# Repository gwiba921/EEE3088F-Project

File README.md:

# EEE3088F-Project
# EEE3088F Project: Power Subsystem for Micro Mouse Robot

## 📌 Introduction

This project forms part of the EEE3088F course, focusing on the design and development of the **power subsystem** for a maze-solving robot known as a **micro mouse**. The micro mouse achieves autonomous navigation through a system modularized into:

- Processor
- Motherboard
- Sensing
- Power

Our responsibility lies in the **Power Module**, which ensures reliable power delivery to all electronic components of the micro mouse.

---

## ⚙️ 1. Problem Description

The micro mouse requires a stable and efficient power supply to drive its operations, which include movement, sensing, and computation. This project involves designing a power module capable of:

- Powering **four DC motors**
- Integrating **USB-C** for **9V output**
- Regulating **3.3V and 5V power rails**
- Enabling **dual battery charging modes**

All of this must be done while maintaining modular compatibility with the rest of the micro mouse system.

---

## 📐 2. Scope and Limitations

- **Scope**:  
  This project is limited to the **power subsystem only**. However, the design must remain compatible with the processor, motherboard, and sensing modules.

- **Constraints**:
  - Strict budget limit of **$70**
  - **No use of breadboard-based components**
  - Must meet **PCB dimension limits**: `82mm x 60mm`
  - Requires **individual reports** despite collaborative PCB design
  - PCB must be designed from scratch using **permitted components only**

---

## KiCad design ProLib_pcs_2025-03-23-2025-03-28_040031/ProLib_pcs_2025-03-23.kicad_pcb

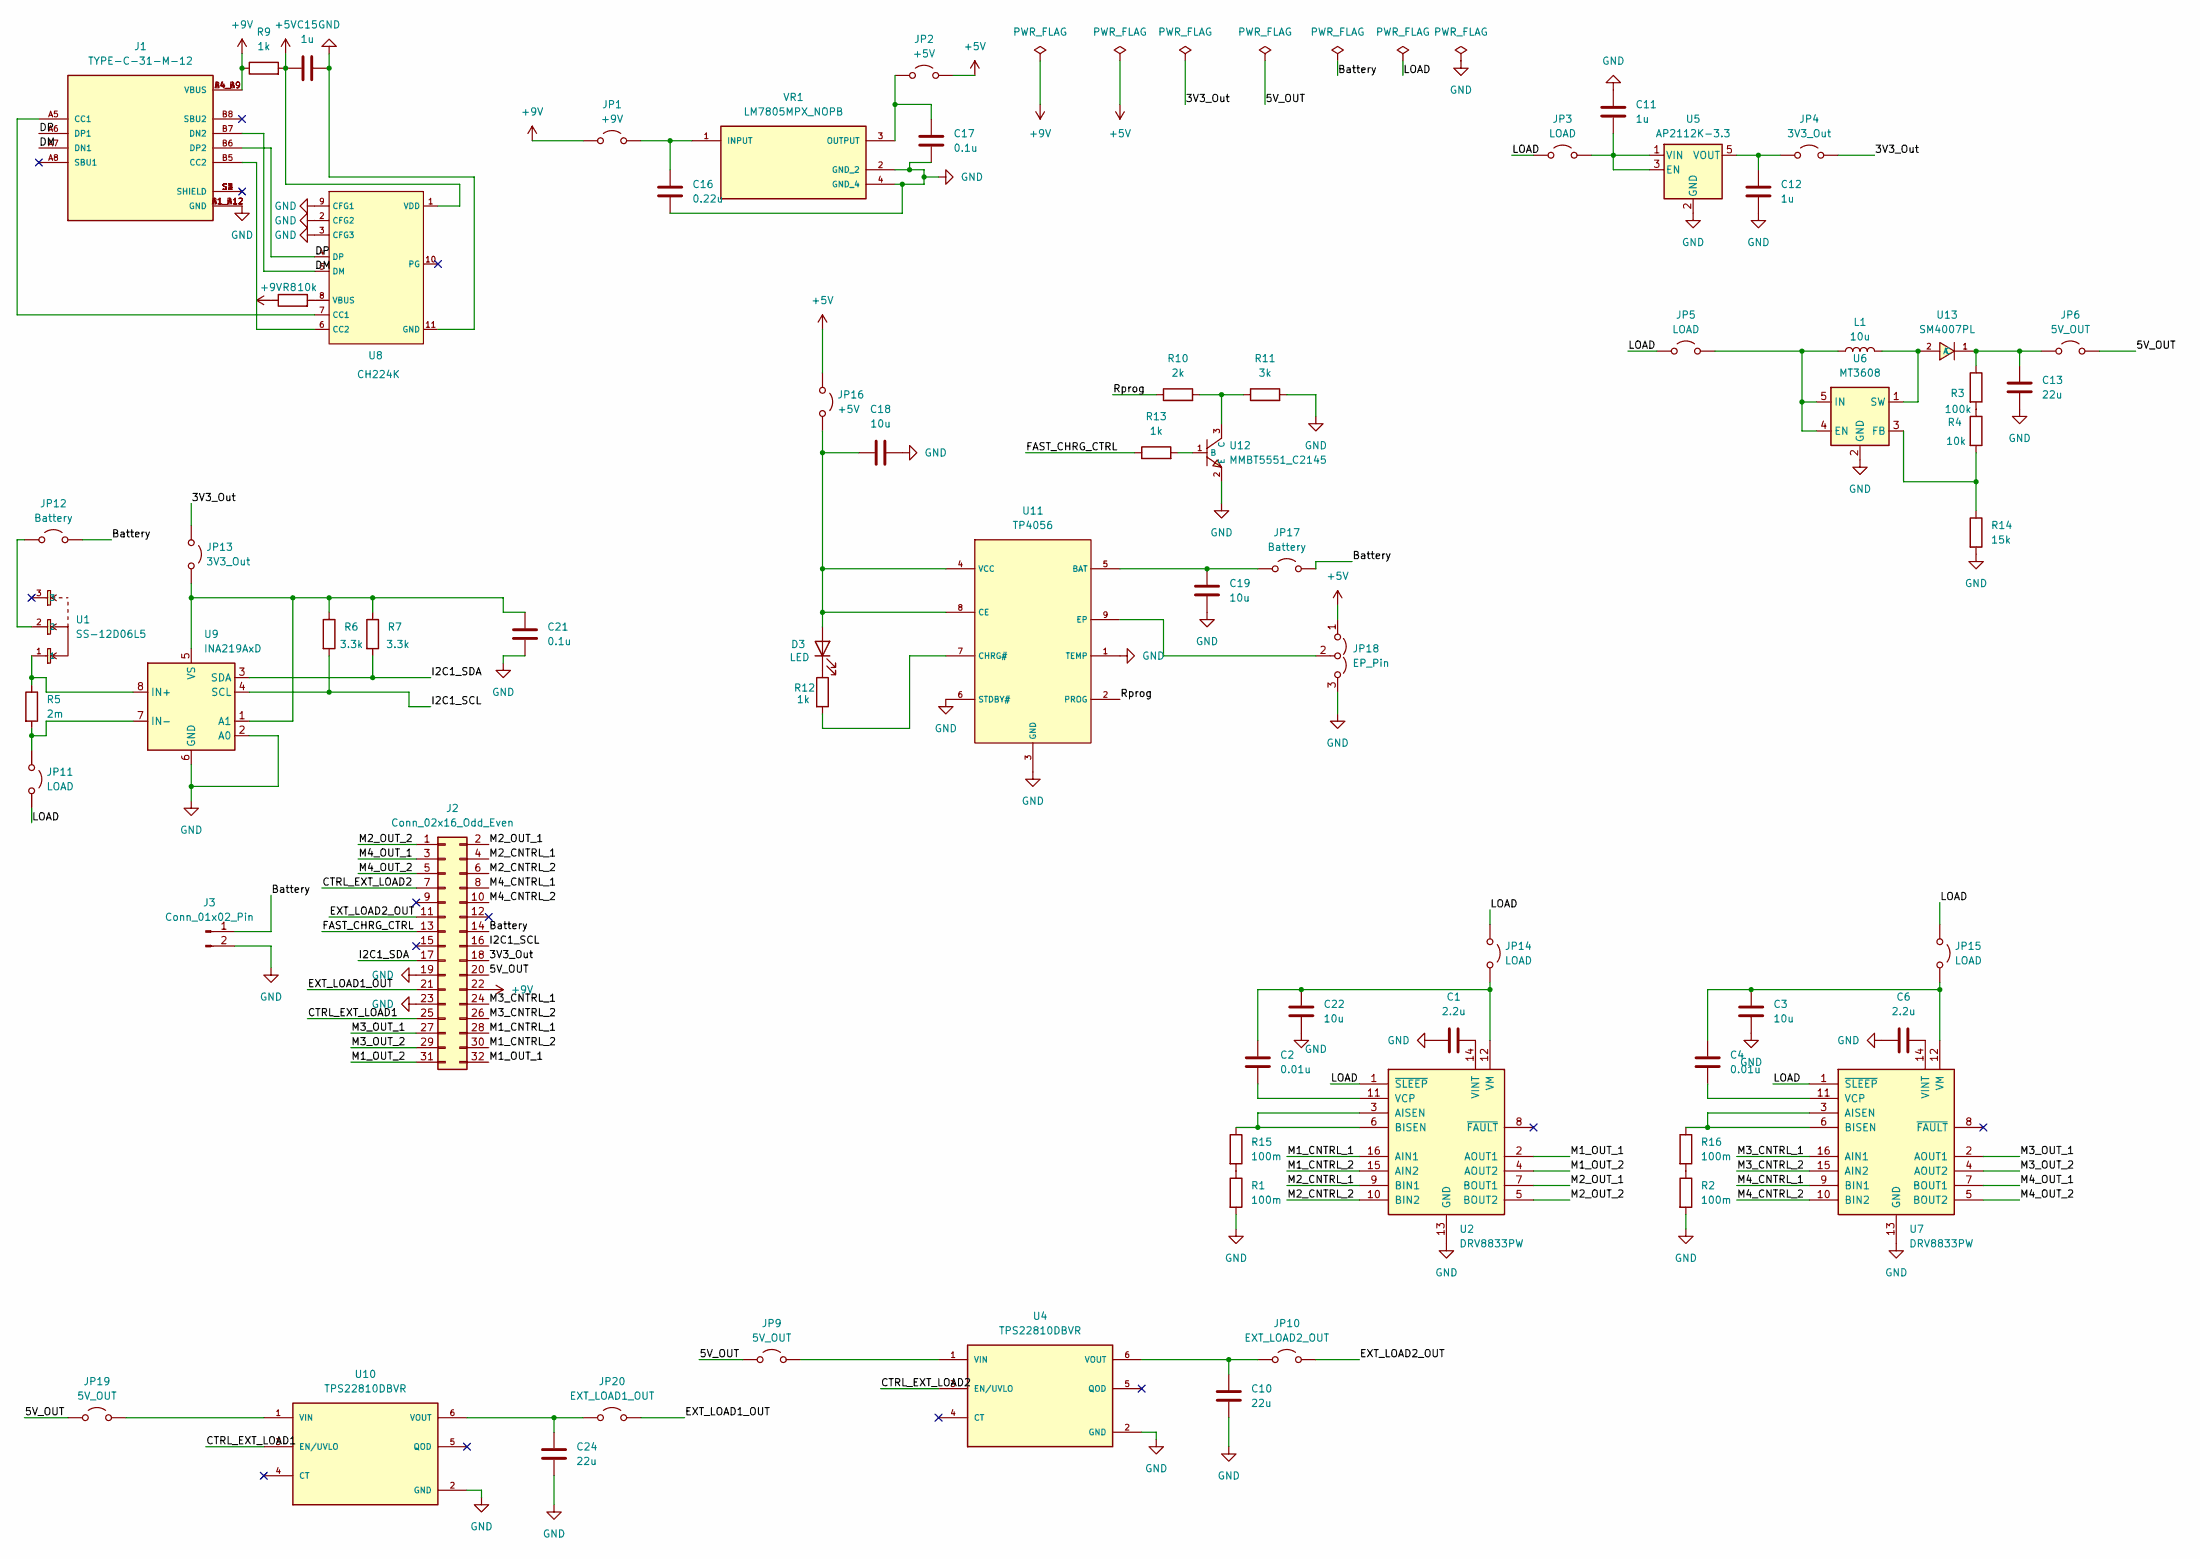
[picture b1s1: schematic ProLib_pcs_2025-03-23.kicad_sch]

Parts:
C1, C6: 2.2u; C_0603_1608Metric_Pad1.08x0.95mm_HandSolder; LCSC C23630
C2, C4: 0.01u; C_0603_1608Metric_Pad1.08x0.95mm_HandSolder; LCSC C57112
C3, C18, C19, C22: 10u; C_0603_1608Metric_Pad1.08x0.95mm_HandSolder; LCSC C19702
C10, C13, C24: 22u; C_0603_1608Metric_Pad1.08x0.95mm_HandSolder; LCSC C59461
C11, C12, C15: 1u; C_0603_1608Metric_Pad1.08x0.95mm_HandSolder; LCSC C15849
C16: 0.22u; C_0603_1608Metric_Pad1.08x0.95mm_HandSolder; LCSC C21120
C17, C21: 0.1u; C_0603_1608Metric_Pad1.08x0.95mm_HandSolder; LCSC C14663
D3: LED; LED_0603_1608Metric_Pad1.05x0.95mm_HandSolder; LCSC C2286
J1: TYPE-C-31-M-12; HRO_TYPE-C-31-M-12; PARTREV 2020.12.08; LCSC C165948
J2: Conn_02x16_Odd_Even; PinHeader_2x16_P2.54mm_Vertical
J3: Conn_01x02_Pin; JST_PH_S2B-PH-K_1x02_P2.00mm_Horizontal
JP1: +9V; SolderJumper-2_P1.3mm_Open_RoundedPad1.0x1.5mm
JP2, JP16: +5V; SolderJumper-2_P1.3mm_Open_RoundedPad1.0x1.5mm
JP3, JP5, JP11, JP14, JP15: LOAD; SolderJumper-2_P1.3mm_Open_RoundedPad1.0x1.5mm
JP4, JP13: 3V3_Out; SolderJumper-2_P1.3mm_Open_RoundedPad1.0x1.5mm
JP6, JP9, JP19: 5V_OUT; SolderJumper-2_P1.3mm_Open_RoundedPad1.0x1.5mm
JP10: EXT_LOAD2_OUT; SolderJumper-2_P1.3mm_Open_RoundedPad1.0x1.5mm
JP12, JP17: Battery; SolderJumper-2_P1.3mm_Open_RoundedPad1.0x1.5mm
JP18: EP_Pin; SolderJumper-3_P1.3mm_Open_RoundedPad1.0x1.5mm
JP20: EXT_LOAD1_OUT; SolderJumper-2_P1.3mm_Open_RoundedPad1.0x1.5mm
L1: 10u; L_0603_1608Metric_Pad1.05x0.95mm_HandSolder; LCSC C1035
R1, R2, R15, R16: 100m; R_1206_3216Metric_Pad1.30x1.75mm_HandSolder; LCSC C25334
R3: 100k; R_0603_1608Metric_Pad0.98x0.95mm_HandSolder; LCSC C25803
R4, R8: 10k; R_0603_1608Metric_Pad0.98x0.95mm_HandSolder; LCSC C25804
R5: 2m; R_2512_6332Metric_Pad1.40x3.35mm_HandSolder; LCSC C2994640
R6, R7: 3.3k; R_0603_1608Metric_Pad0.98x0.95mm_HandSolder; LCSC C22978
R9, R12, R13: 1k; R_0603_1608Metric_Pad0.98x0.95mm_HandSolder; LCSC C21190
R10: 2k; R_0603_1608Metric_Pad0.98x0.95mm_HandSolder; LCSC C22975
R11: 3k; R_0603_1608Metric_Pad0.98x0.95mm_HandSolder; LCSC C4211
R14: 15k; R_0603_1608Metric_Pad0.98x0.95mm_HandSolder; LCSC C22809
U1: SS-12D06L5; SW-TH_3P-P4.70_L11.1-W12.7; LCSC C319015
U2, U7: DRV8833PW; TSSOP-16_4.4x5mm_P0.65mm; LCSC C50506
U4, U10: TPS22810DBVR; SOT95P280X145-6N; PARTREV C; LCSC C205990
U5: AP2112K-3.3; SOT-23-5; LCSC C23380830
U6: MT3608; SOT-23-6; LCSC C19189893
U8: CH224K; ESSOP-10_L4.9-W3.9-P1.0-LS6.0-TL-EP; LCSC C970725
U9: INA219AxD; SOIC-8_3.9x4.9mm_P1.27mm; LCSC C138706
U11: TP4056; ESOP-8_L4.9-W3.9-P1.27-LS6.0-BL-EP; LCSC C16581
U12: MMBT5551_C2145; SOT-23-3_L2.9-W1.3-P1.90-LS2.4-BR; LCSC C2145
U13: SM4007PL; SOD-123F_L2.8-W1.8-LS3.7-RD; LCSC C64898
VR1: LM7805MPX_NOPB; VREG_LM7805MPX_NOPB; PARTREV L; LCSC C2848241

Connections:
+5V: C15.1, JP2.2 (B), JP16.1 (A), JP18.1 (A), R9.2, U8.1 (VDD)
+9V: J1.A4_B9 (VBUS), J1.B4_A9 (VBUS), J2.22, JP1.1 (A), R8.1, R9.1
/3V3_Out: J2.18, JP4.2 (B), JP13.1 (A)
/5V_OUT: J2.20, JP6.2 (B), JP9.1 (A), JP19.1 (A)
/Battery: J2.14, J3.1, JP12.2 (B), JP17.2 (B)
/CTRL_EXT_LOAD1: J2.25, U10.3 (EN/UVLO)
/CTRL_EXT_LOAD2: J2.7, U4.3 (EN/UVLO)
/DM: J1.A7 (DN1), J1.B7 (DN2), U8.5 (DM)
/DP: J1.A6 (DP1), J1.B6 (DP2), U8.4 (DP)
/EXT_LOAD1_OUT: J2.21, JP20.2 (B)
/EXT_LOAD2_OUT: J2.11, JP10.2 (B)
/FAST_CHRG_CTRL: J2.13, R13.1
/I2C1_SCL: J2.16, R6.2, U9.4 (SCL)
/I2C1_SDA: J2.17, R7.2, U9.3 (SDA)
/LOAD: JP3.1 (A), JP5.1 (A), JP11.2 (B), JP14.1 (A), JP15.1 (A), U2.1 (~SLEEP), U7.1 (~SLEEP)
/M1_CNTRL_1: J2.28, U2.16 (AIN1)
/M1_CNTRL_2: J2.30, U2.15 (AIN2)
/M1_OUT_1: J2.32, U2.2 (AOUT1)
/M1_OUT_2: J2.31, U2.4 (AOUT2)
/M2_CNTRL_1: J2.4, U2.9 (BIN1)
/M2_CNTRL_2: J2.6, U2.10 (BIN2)
/M2_OUT_1: J2.2, U2.7 (BOUT1)
/M2_OUT_2: J2.1, U2.5 (BOUT2)
/M3_CNTRL_1: J2.24, U7.16 (AIN1)
/M3_CNTRL_2: J2.26, U7.15 (AIN2)
/M3_OUT_1: J2.27, U7.2 (AOUT1)
/M3_OUT_2: J2.29, U7.4 (AOUT2)
/M4_CNTRL_1: J2.8, U7.9 (BIN1)
/M4_CNTRL_2: J2.10, U7.10 (BIN2)
/M4_OUT_1: J2.3, U7.7 (BOUT1)
/M4_OUT_2: J2.5, U7.5 (BOUT2)
/Rprog: R10.1, U11.2 (PROG)
GND: C1.1, C3.2, C6.1, C10.2, C11.1, C12.2, C13.2, C15.2, C16.2, C17.2, C18.2, C19.2, C21.2, C22.2, C24.2, J1.A1_B12 (GND), J1.B1_A12 (GND), J2.19, J2.23, J3.2, JP18.3 (B), R1.2, R2.2, R11.2, R14.2, U2.13 (GND), U4.2 (GND), U5.2 (GND), U6.2 (GND), U7.13 (GND), U8.2 (CFG2), U8.3 (CFG3), U8.9 (CFG1), U8.11 (GND), U9.2 (A0), U9.6 (GND), U10.2 (GND), U11.1 (TEMP), U11.3 (GND), U11.6 (STDBY#), U12.2 (E), VR1.2 (GND_2), VR1.4 (GND_4)
unnamed: C18.1, D3.2 (A), JP16.2 (B), U11.4 (VCC), U11.8 (CE)
unnamed: D3.1 (K), R12.1
unnamed: J1.A5 (CC1), U8.7 (CC1)
unnamed: J1.B5 (CC2), U8.6 (CC2)
unnamed: C16.1, JP1.2 (B), VR1.1 (INPUT)
unnamed: C17.1, JP2.1 (A), VR1.3 (OUTPUT)
unnamed: C11.2, JP3.2 (B), U5.1 (VIN), U5.3 (EN)
unnamed: C12.1, JP4.1 (A), U5.5 (VOUT)
unnamed: JP5.2 (B), L1.1, U6.4 (EN), U6.5 (IN)
unnamed: C13.1, JP6.1 (A), R3.1, U13.1 (C)
unnamed: JP9.2 (B), U4.1 (VIN)
unnamed: C10.1, JP10.1 (A), U4.6 (VOUT)
unnamed: JP11.1 (A), R5.2, U9.7 (IN-)
unnamed: JP12.1 (A), U1.2
unnamed: C21.1, JP13.2 (B), R6.1, R7.1, U9.1 (A1), U9.5 (VS)
unnamed: C2.1, C22.1, JP14.2 (B), U2.12 (VM)
unnamed: C3.1, C4.1, JP15.2 (B), U7.12 (VM)
unnamed: C19.1, JP17.1 (A), U11.5 (BAT)
unnamed: JP18.2 (C), U11.9 (EP)
unnamed: JP19.2 (B), U10.1 (VIN)
unnamed: C24.1, JP20.1 (A), U10.6 (VOUT)
unnamed: R1.1, R15.2
unnamed: R3.2, R4.1
unnamed: R2.1, R16.2
unnamed: R15.1, U2.3 (AISEN), U2.6 (BISEN)
unnamed: C2.2, U2.11 (VCP)
unnamed: C1.2, U2.14 (VINT)
unnamed: R4.2, R14.1, U6.3 (FB)
unnamed: R16.1, U7.3 (AISEN), U7.6 (BISEN)
unnamed: C4.2, U7.11 (VCP)
unnamed: C6.2, U7.14 (VINT)
unnamed: R8.2, U8.8 (VBUS)
unnamed: R5.1, U1.1, U9.8 (IN+)
unnamed: R12.2, U11.7 (CHRG#)
unnamed: R13.2, U12.1 (B)
unnamed: R10.2, R11.1, U12.3 (C)
unnamed: L1.2, U6.1 (SW), U13.2 (A)

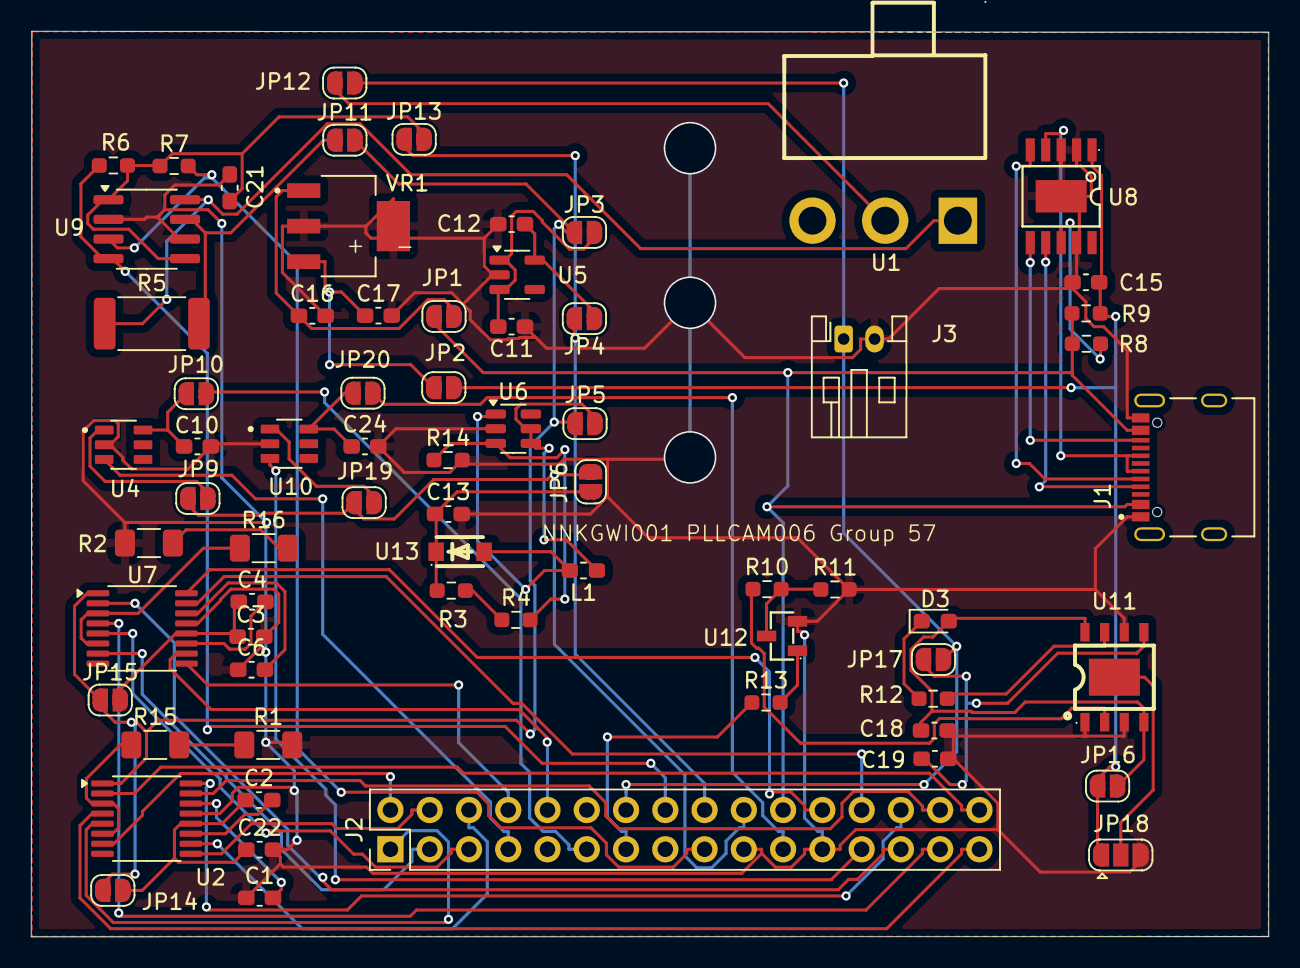
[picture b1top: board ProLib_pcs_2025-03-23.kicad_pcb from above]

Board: 2 copper layers, 80.0 x 58.6 mm, 69 parts (0 on the bottom side), 70 nets.

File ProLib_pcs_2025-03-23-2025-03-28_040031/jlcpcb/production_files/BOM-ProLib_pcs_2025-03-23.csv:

Comment,Designator,Footprint,LCSC,Quantity
10u,L1,L_0603_1608Metric_Pad1.05x0.95mm_HandSolder,C1035,1
INA219AxD,U9,SOIC-8_3.9x4.9mm_P1.27mm,C138706,1
0.1u,"C17,C21",C_0603_1608Metric_Pad1.08x0.95mm_HandSolder,C14663,2
1u,"C11,C12,C15",C_0603_1608Metric_Pad1.08x0.95mm_HandSolder,C15849,3
TP4056,U11,ESOP-8_L4.9-W3.9-P1.27-LS6.0-BL-EP,C16581,1
TYPE-C-31-M-12,J1,HRO_TYPE-C-31-M-12,C165948,1
MT3608,U6,SOT-23-6,C19189893,1
10u,"C18,C19,C22,C3",C_0603_1608Metric_Pad1.08x0.95mm_HandSolder,C19702,4
TPS22810DBVR,"U10,U4",SOT95P280X145-6N,C205990,2
0.22u,C16,C_0603_1608Metric_Pad1.08x0.95mm_HandSolder,C21120,1
1k,"R12,R13,R9",R_0603_1608Metric_Pad0.98x0.95mm_HandSolder,C21190,3
MMBT5551_C2145,U12,SOT-23-3_L2.9-W1.3-P1.90-LS2.4-BR,C2145,1
15k,R14,R_0603_1608Metric_Pad0.98x0.95mm_HandSolder,C22809,1
LED,D3,LED_0603_1608Metric_Pad1.05x0.95mm_HandSolder,C2286,1
2k,R10,R_0603_1608Metric_Pad0.98x0.95mm_HandSolder,C22975,1
3.3k,"R6,R7",R_0603_1608Metric_Pad0.98x0.95mm_HandSolder,C22978,2
AP2112K-3.3,U5,SOT-23-5,C23380830,1
2.2u,"C1,C6",C_0603_1608Metric_Pad1.08x0.95mm_HandSolder,C23630,2
100k,R3,R_0603_1608Metric_Pad0.98x0.95mm_HandSolder,C25803,1
10k,"R4,R8",R_0603_1608Metric_Pad0.98x0.95mm_HandSolder,C25804,2
LM7805MPX_NOPB,VR1,VREG_LM7805MPX_NOPB,C2848241,1
2m,R5,R_2512_6332Metric_Pad1.40x3.35mm_HandSolder,C2994640,1
SS-12D06L5,U1,SW-TH_3P-P4.70_L11.1-W12.7,C319015,1
3k,R11,R_0603_1608Metric_Pad0.98x0.95mm_HandSolder,C4211,1
DRV8833PW,"U2,U7",TSSOP-16_4.4x5mm_P0.65mm,C50506,2
0.01u,"C2,C4",C_0603_1608Metric_Pad1.08x0.95mm_HandSolder,C57112,2
22u,"C10,C13,C24",C_0603_1608Metric_Pad1.08x0.95mm_HandSolder,C59461,3
SM4007PL,U13,SOD-123F_L2.8-W1.8-LS3.7-RD,C64898,1
CH224K,U8,ESSOP-10_L4.9-W3.9-P1.0-LS6.0-TL-EP,C970725,1
100m,R2,R_1206_3216Metric_Pad1.30x1.75mm_HandSolder,C25334,1
100m,R1,R_1206_3216Metric_Pad1.30x1.75mm_HandSolder,C25334,1
100m,R15,R_1206_3216Metric_Pad1.30x1.75mm_HandSolder,C25334,1
100m,R16,R_1206_3216Metric_Pad1.30x1.75mm_HandSolder,C25334,1

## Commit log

2025-04-25 kicad final commit
